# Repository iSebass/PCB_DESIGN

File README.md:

# PCB_DESIGN
En este repositorio encontraremos todo lo que refiere al desarrollo de PCB.

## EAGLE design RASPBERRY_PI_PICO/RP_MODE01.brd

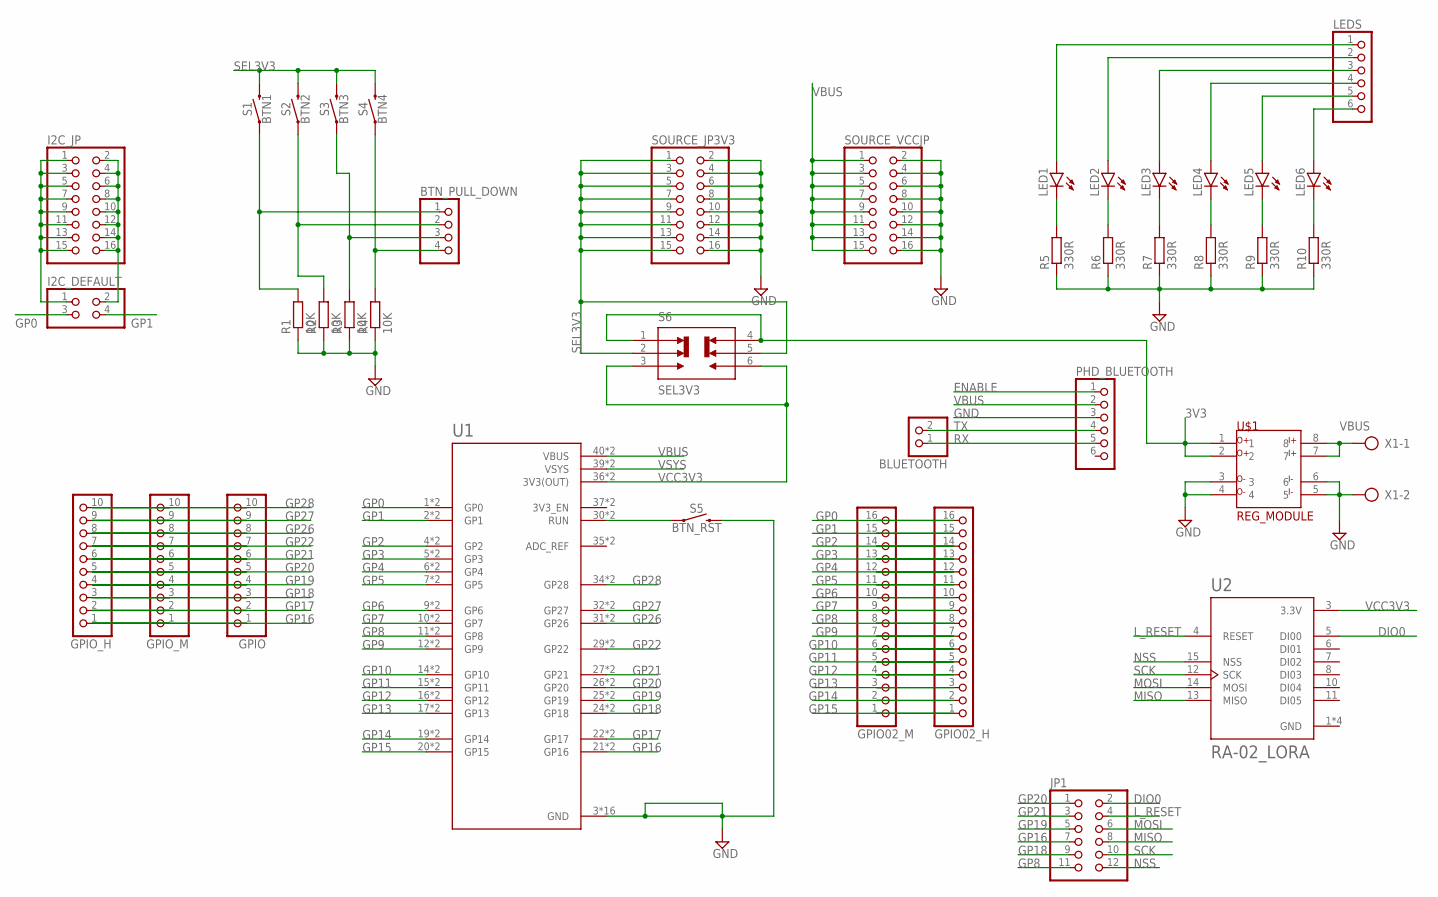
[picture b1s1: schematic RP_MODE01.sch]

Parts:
BLUETOOTH: PINHD-1X2; 1X02
BTN_PULL_DOWN: PINHD-1X4; 1X04
GPIO: PINHD-1X10; 1X10
GPIO02_H, GPIO02_M: PINHD-1X16; 1X16
GPIO_H: PINHD-1X10; 1X10
GPIO_M: PINHD-1X10; 1X10
I2C_DEFAULT: PINHD-2X2; 2X02
I2C_JP: PINHD-2X8; 2X08
JP1: PINHD-2X6; 2X06
LED1, LED2, LED3, LED4, LED5, LED6: LEDCHIP-LED0805; CHIP-LED0805
LEDS: PINHD-1X6; 1X06
PHD_BLUETOOTH: PINHD-1X6; 1X06
R1, R2, R3, R4: 10K; R0805
R5, R6, R7, R8, R9, R10: 330R; R0805
S1: BTN1; TACTILE_SWITCH_SMD_6.0X3.5MM
S2: BTN2; TACTILE_SWITCH_SMD_6.0X3.5MM
S3: BTN3; TACTILE_SWITCH_SMD_6.0X3.5MM
S4: BTN4; TACTILE_SWITCH_SMD_6.0X3.5MM
S5: BTN_RST; TACTILE_SWITCH_SMD_6.0X3.5MM
S6: SEL3V3; SW_JS202011SCQN
SOURCE_JP3V3: PINHD-2X8; 2X08
SOURCE_VCCJP: PINHD-2X8; 2X08
U1: RASPBERRY_PICO-NO_DEBUG; PICO-PKG-NO_DEBUG
U2: RA-02_LORA; MODULE_RA-02_LORA
U$1: REG_MODULE
X1: AK300/2

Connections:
3V3: S6.1, S6.4, U$1.1, U$1.2
DIO0: JP1.2, U2.5 (DI00)
ENABLE: PHD_BLUETOOTH.1
GND: PHD_BLUETOOTH.3, R1.1, R2.1, R3.1, R4.1, R5.1, R6.1, R7.1, R8.1, R9.1, R10.1, S5.2, SOURCE_JP3V3.2, SOURCE_JP3V3.4, SOURCE_JP3V3.6, SOURCE_JP3V3.8, SOURCE_JP3V3.10, SOURCE_JP3V3.12, SOURCE_JP3V3.14, SOURCE_JP3V3.16, SOURCE_VCCJP.2, SOURCE_VCCJP.4, SOURCE_VCCJP.6, SOURCE_VCCJP.8, SOURCE_VCCJP.10, SOURCE_VCCJP.12, SOURCE_VCCJP.14, SOURCE_VCCJP.16, U1.3 (GND), U1.8 (GND), U1.13 (GND), U1.18 (GND), U1.23 (GND), U1.28 (GND), U1.33 (GND), U1.38 (GND), U1.P$3 (GND), U1.P$8 (GND), U1.P$13 (GND), U1.P$18 (GND), U1.P$23 (GND), U1.P$28 (GND), U1.P$33 (GND), U1.P$38 (GND), U2.1 (GND), U2.2 (GND), U2.9 (GND), U2.16 (GND), U$1.3, U$1.4, U$1.5, U$1.6, X1.2
GP0: GPIO02_H.16, GPIO02_M.16, I2C_DEFAULT.3, U1.1 (GP0), U1.P$1 (GP0)
GP1: GPIO02_H.15, GPIO02_M.15, I2C_DEFAULT.4, U1.2 (GP1), U1.P$2 (GP1)
GP2: GPIO02_H.14, GPIO02_M.14, U1.4 (GP2), U1.P$4 (GP2)
GP3: GPIO02_H.13, GPIO02_M.13, U1.5 (GP3), U1.P$5 (GP3)
GP4: GPIO02_H.12, GPIO02_M.12, U1.6 (GP4), U1.P$6 (GP4)
GP5: GPIO02_H.11, GPIO02_M.11, U1.7 (GP5), U1.P$7 (GP5)
GP6: GPIO02_H.10, GPIO02_M.10, U1.9 (GP6), U1.P$9 (GP6)
GP7: GPIO02_H.9, GPIO02_M.9, U1.10 (GP7), U1.P$10 (GP7)
GP8: GPIO02_H.8, GPIO02_M.8, JP1.11, U1.11 (GP8), U1.P$11 (GP8)
GP9: GPIO02_H.7, GPIO02_M.7, U1.12 (GP9), U1.P$12 (GP9)
GP10: GPIO02_H.6, GPIO02_M.6, U1.14 (GP10), U1.P$14 (GP10)
GP11: GPIO02_H.5, GPIO02_M.5, U1.15 (GP11), U1.P$15 (GP11)
GP12: GPIO02_H.4, GPIO02_M.4, U1.16 (GP12), U1.P$16 (GP12)
GP13: GPIO02_H.3, GPIO02_M.3, U1.17 (GP13), U1.P$17 (GP13)
GP14: GPIO02_H.2, GPIO02_M.2, U1.19 (GP14), U1.P$19 (GP14)
GP15: GPIO02_H.1, GPIO02_M.1, U1.20 (GP15), U1.P$20 (GP15)
GP16: GPIO.1, GPIO_H.1, GPIO_M.1, JP1.7, U1.21 (GP16), U1.P$21 (GP16)
GP17: GPIO.2, GPIO_H.2, GPIO_M.2, U1.22 (GP17), U1.P$22 (GP17)
GP18: GPIO.3, GPIO_H.3, GPIO_M.3, JP1.9, U1.24 (GP18), U1.P$24 (GP18)
GP19: GPIO.4, GPIO_H.4, GPIO_M.4, JP1.5, U1.25 (GP19), U1.P$25 (GP19)
GP20: GPIO.5, GPIO_H.5, GPIO_M.5, JP1.1, U1.26 (GP20), U1.P$26 (GP20)
GP21: GPIO.6, GPIO_H.6, GPIO_M.6, JP1.3, U1.27 (GP21), U1.P$27 (GP21)
GP22: GPIO.7, GPIO_H.7, GPIO_M.7, U1.29 (GP22), U1.P$29 (GP22)
GP26: GPIO.8, GPIO_H.8, GPIO_M.8, U1.31 (GP26), U1.P$31 (GP26)
GP27: GPIO.9, GPIO_H.9, GPIO_M.9, U1.32 (GP27), U1.P$32 (GP27)
GP28: GPIO.10, GPIO_H.10, GPIO_M.10, U1.34 (GP28), U1.P$34 (GP28)
L_RESET: JP1.4, U2.4 (RESET)
MISO: JP1.8, U2.13 (MISO)
MOSI: JP1.6, U2.14 (MOSI)
unnamed: BTN_PULL_DOWN.1, R1.2, S1.1
unnamed: BTN_PULL_DOWN.2, R2.2, S2.1
unnamed: BTN_PULL_DOWN.3, R3.2, S3.1
unnamed: BTN_PULL_DOWN.4, R4.2, S4.1
unnamed: S5.1, U1.30 (RUN), U1.P$30 (RUN)
unnamed: LED2.A, LEDS.2
unnamed: LED3.A, LEDS.3
unnamed: LED1.C, R5.2
unnamed: LED2.C, R6.2
unnamed: LED3.C, R7.2
unnamed: LED4.C, R8.2
unnamed: LED5.C, R9.2
unnamed: LED6.C, R10.2
unnamed: LED6.A, LEDS.6
unnamed: LED1.A, LEDS.1
unnamed: LED4.A, LEDS.4
unnamed: LED5.A, LEDS.5
NSS: JP1.12, U2.15 (NSS)
RX: BLUETOOTH.1, PHD_BLUETOOTH.5
SCK: JP1.10, U2.12 (SCK)
SCL: I2C_DEFAULT.2, I2C_JP.2, I2C_JP.4, I2C_JP.6, I2C_JP.8, I2C_JP.10, I2C_JP.12, I2C_JP.14, I2C_JP.16
SDA: I2C_DEFAULT.1, I2C_JP.1, I2C_JP.3, I2C_JP.5, I2C_JP.7, I2C_JP.9, I2C_JP.11, I2C_JP.13, I2C_JP.15
SEL3V3: S1.2, S2.2, S3.2, S4.2, S6.2, S6.5, SOURCE_JP3V3.1, SOURCE_JP3V3.3, SOURCE_JP3V3.5, SOURCE_JP3V3.7, SOURCE_JP3V3.9, SOURCE_JP3V3.11, SOURCE_JP3V3.13, SOURCE_JP3V3.15
TX: BLUETOOTH.2, PHD_BLUETOOTH.4
VBUS: PHD_BLUETOOTH.2, SOURCE_VCCJP.1, SOURCE_VCCJP.3, SOURCE_VCCJP.5, SOURCE_VCCJP.7, SOURCE_VCCJP.9, SOURCE_VCCJP.11, SOURCE_VCCJP.13, SOURCE_VCCJP.15, U1.40 (VBUS), U1.P$40 (VBUS), U$1.7, U$1.8, X1.1
VCC3V3: S6.3, S6.6, U1.36 (3V3(OUT)), U1.P$36 (3V3(OUT)), U2.3 (3.3V)
VSYS: U1.39 (VSYS), U1.P$39 (VSYS)

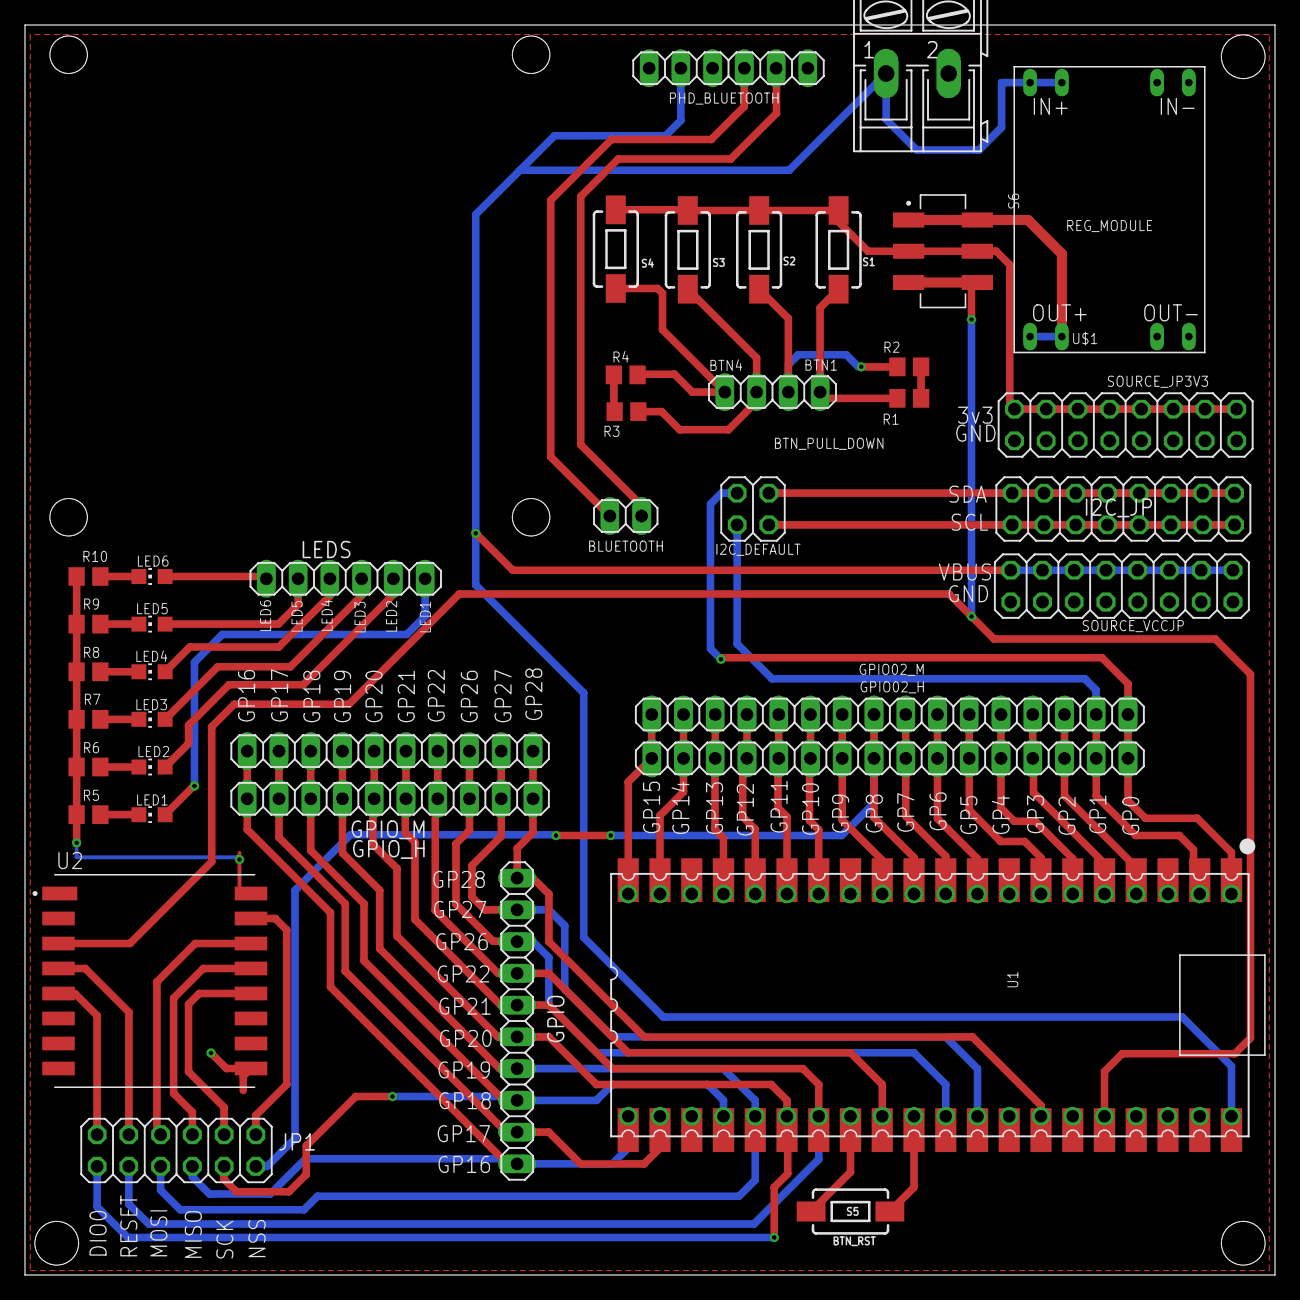
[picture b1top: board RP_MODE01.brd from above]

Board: 2 copper layers, 100.0 x 100.0 mm, 40 parts (0 on the bottom side), 59 nets.

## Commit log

2023-10-23 Se agrega codigo correspondientes a la PCB de TI
2023-10-26 Se actualiza PCB
